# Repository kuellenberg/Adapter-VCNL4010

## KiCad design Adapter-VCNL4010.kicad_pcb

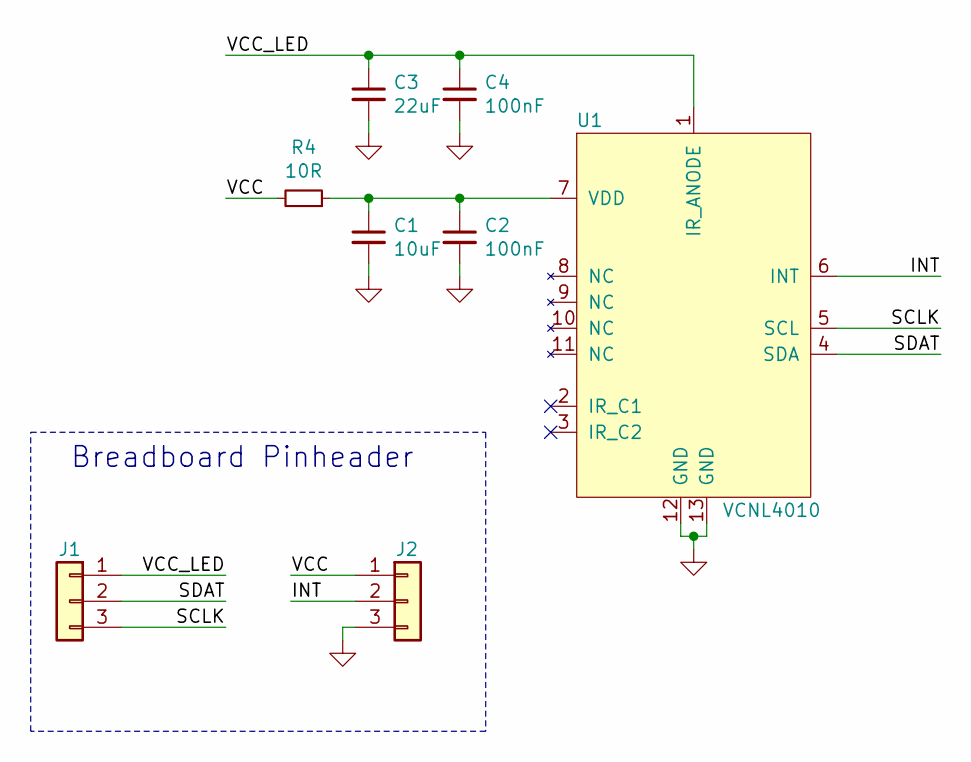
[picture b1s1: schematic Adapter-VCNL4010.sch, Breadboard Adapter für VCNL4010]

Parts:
C1: 10uF; C_0805_2012Metric_Pad1.18x1.45mm_HandSolder
C2, C4: 100nF; C_0805_2012Metric_Pad1.18x1.45mm_HandSolder
C3: 22uF; C_0805_2012Metric_Pad1.18x1.45mm_HandSolder
J1, J2: Conn_01x03; PinHeader_1x03_P2.54mm_Vertical
R4: 10R; R_0805_2012Metric_Pad1.20x1.40mm_HandSolder
U1: VCNL4010; VCNL4010_HS

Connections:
/INT: J2.2, U1.6 (INT)
/SCLK: J1.3, U1.5 (SCL)
/SDAT: J1.2, U1.4 (SDA)
/VCC: J2.1, R4.2
/VCC_LED: C3.1, C4.1, J1.1, U1.1 (IR_ANODE)
GND: C1.2, C2.2, C3.2, C4.2, J2.3, U1.12 (GND), U1.13 (GND)
unnamed: C1.1, C2.1, R4.1, U1.7 (VDD)

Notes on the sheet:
Breadboard Pinheader

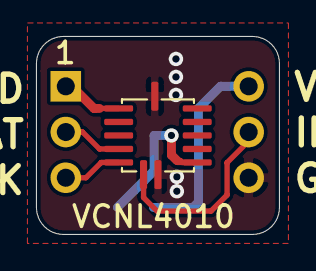
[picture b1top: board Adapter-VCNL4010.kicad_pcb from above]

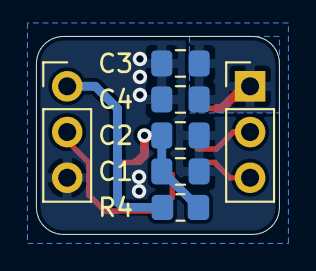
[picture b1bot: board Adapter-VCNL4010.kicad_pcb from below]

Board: 2 copper layers, 13.5 x 11.0 mm, 8 parts (7 on the bottom side), 7 nets.

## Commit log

2021-11-22 Created gerbers
2021-12-04 added PDF
